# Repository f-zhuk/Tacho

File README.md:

# Tacho
ER11 spindle tachometer with rotating display output

Demonstration video:
https://youtu.be/U8TMPHPOaX0?si=c8lLyx_i4HfSOsvz

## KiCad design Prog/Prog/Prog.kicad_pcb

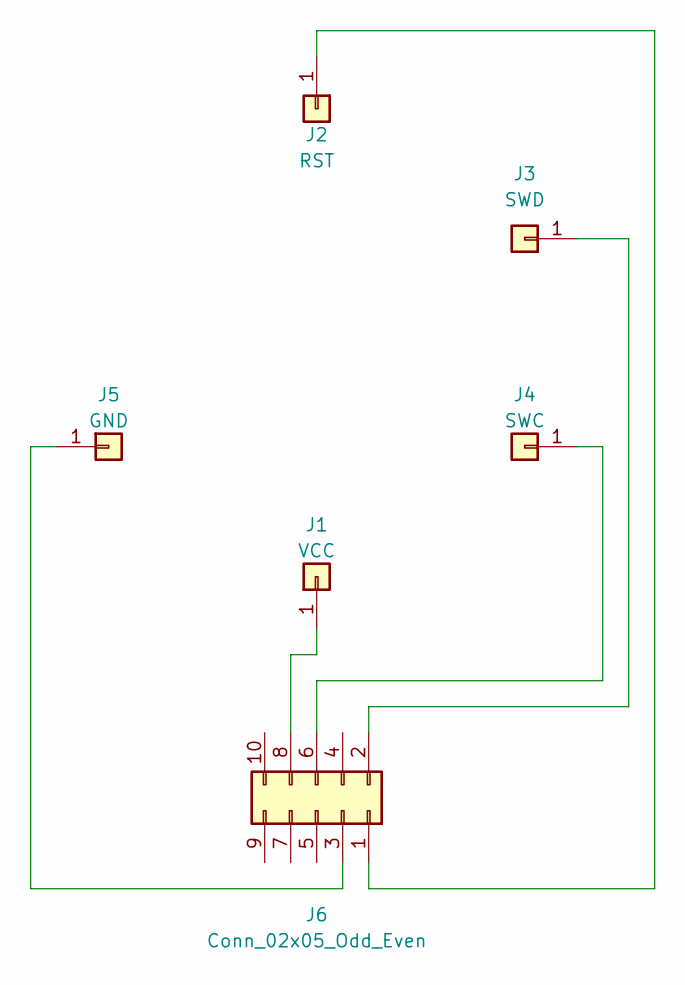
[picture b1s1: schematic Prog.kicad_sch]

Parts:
J1: VCC; PinHeader_1x01_P2.54mm_Vertical
J2: RST; PinHeader_1x01_P2.54mm_Vertical
J3: SWD; PinHeader_1x01_P2.54mm_Vertical
J4: SWC; PinHeader_1x01_P2.54mm_Vertical
J5: GND; PinHeader_1x01_P2.54mm_Vertical
J6: Conn_02x05_Odd_Even; IDC-Header_2x05_P2.54mm_Vertical

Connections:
unnamed: J1.1, J6.8
unnamed: J2.1, J6.1
unnamed: J3.1, J6.2
unnamed: J4.1, J6.6
unnamed: J5.1, J6.3

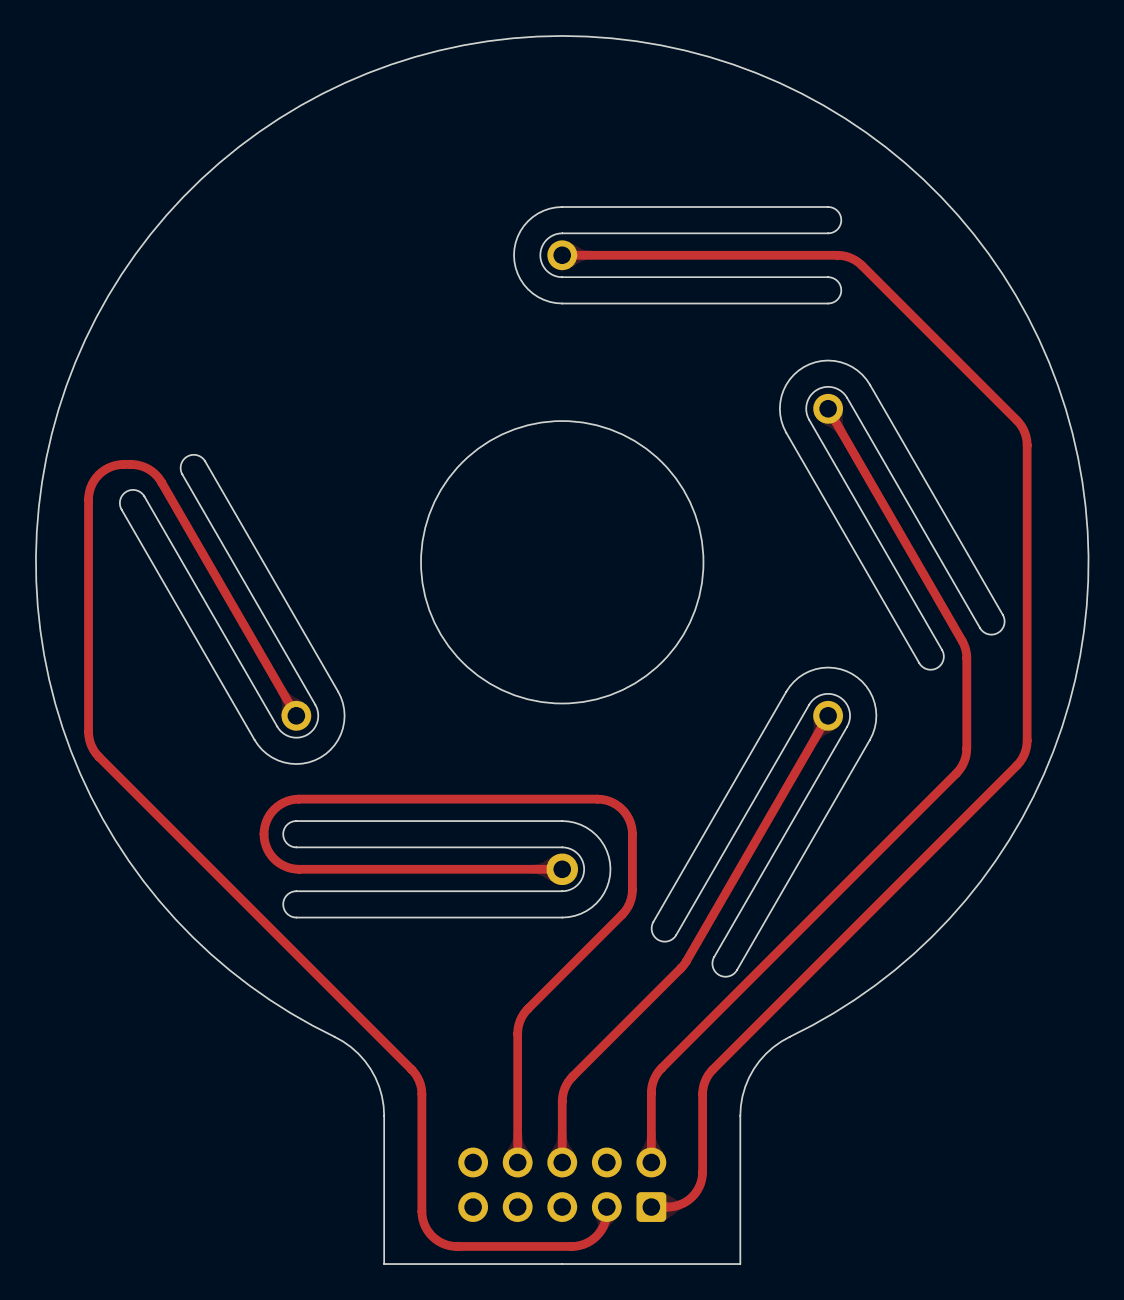
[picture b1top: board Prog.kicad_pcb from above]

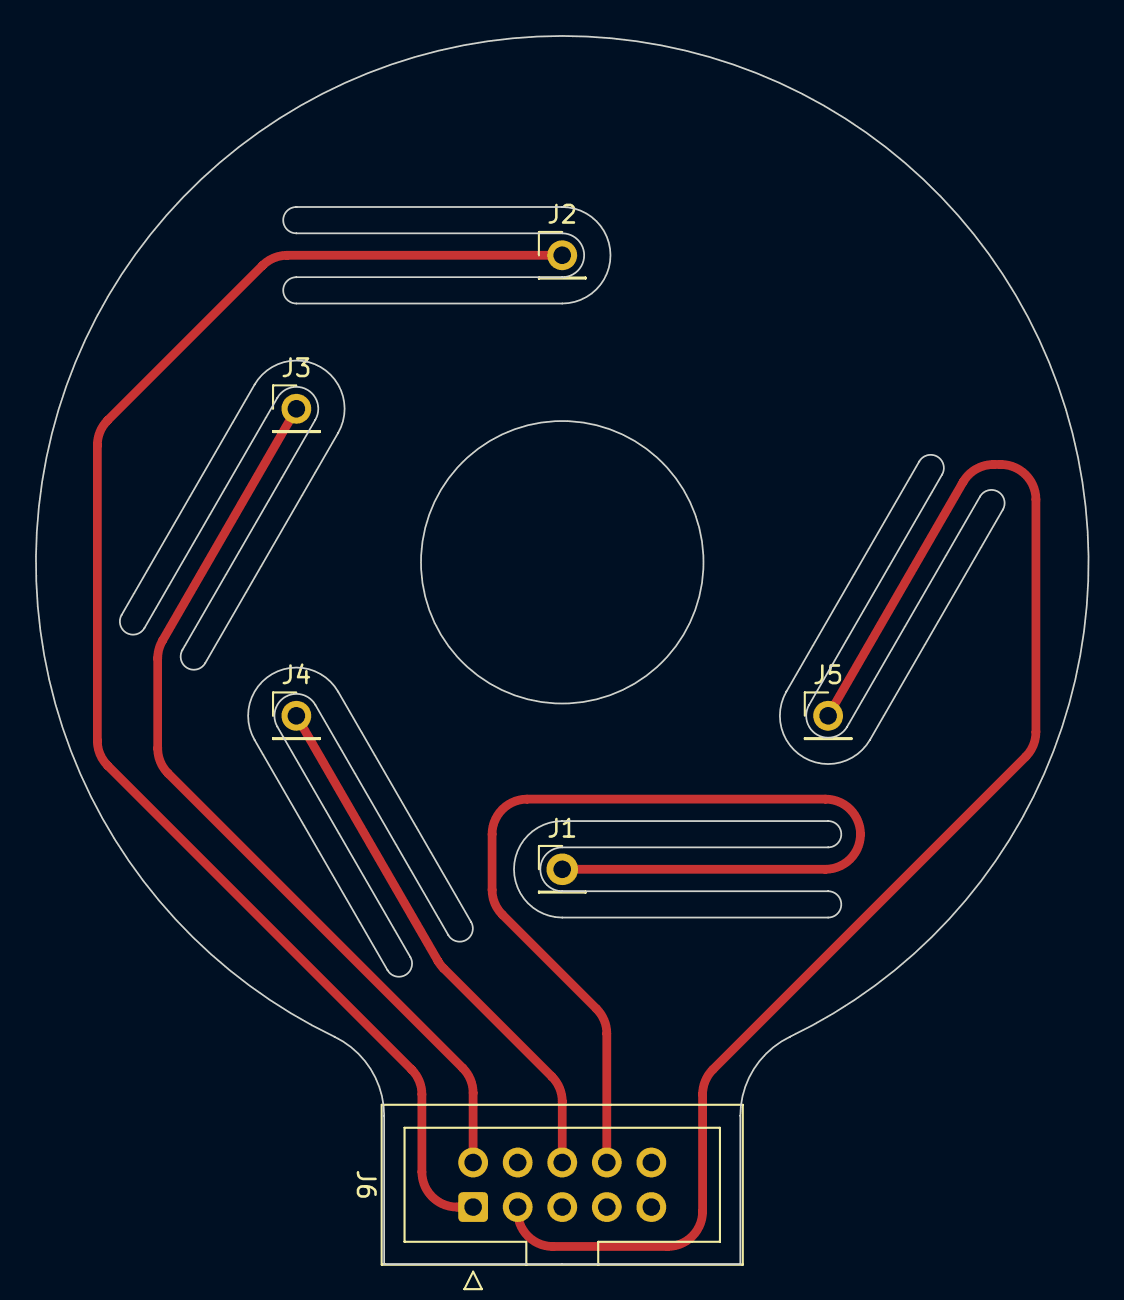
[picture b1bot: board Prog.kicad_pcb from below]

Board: 2 copper layers, 60.0 x 70.0 mm, 6 parts (6 on the bottom side), 5 nets.

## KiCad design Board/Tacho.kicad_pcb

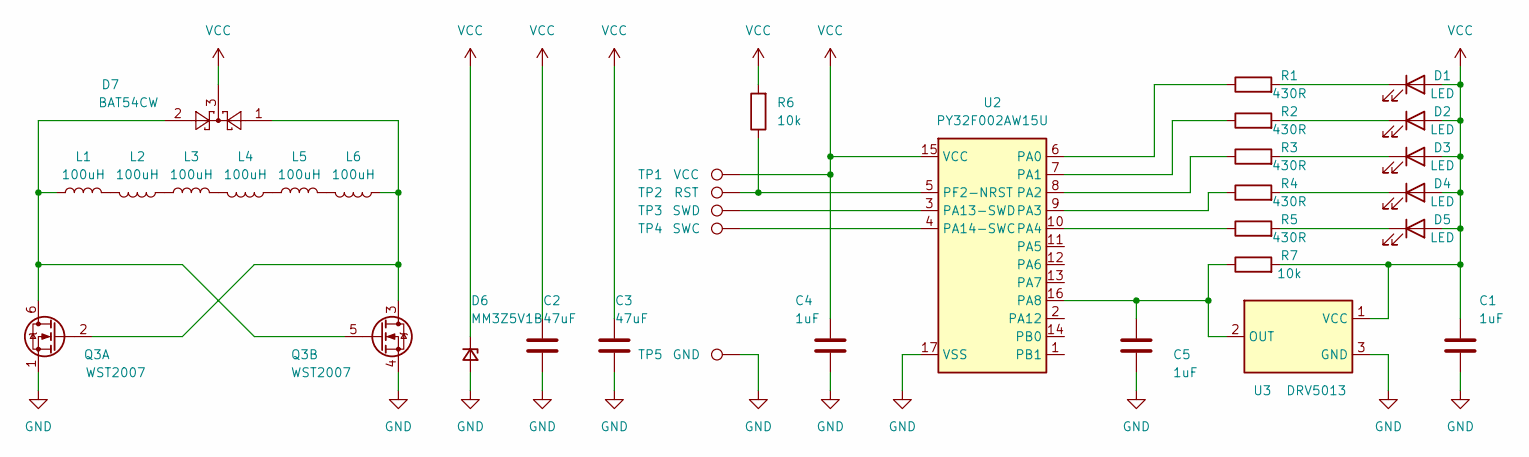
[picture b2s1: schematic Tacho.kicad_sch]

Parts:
C1, C4, C5: 1uF; C_0402_1005Metric_Pad0.74x0.62mm_HandSolder
C2, C3: 47uF; C_0805_2012Metric_Pad1.18x1.45mm_HandSolder
D1, D2, D3, D4, D5: LED; LED_0402_1005Metric
D6: MM3Z5V1B; D_SOD-323
D7: BAT54CW; SOT-323_SC-70
L1, L2, L3, L4, L5, L6: 100uH; L_SHOUHAN _CY43-100UH
Q3: WST2007; SOT-363_SC-70-6
R1, R2, R3, R4, R5: 430R; R_0402_1005Metric
R6, R7: 10k; R_0402_1005Metric
TP1: VCC; TestPoint_Pad_D2.0mm
TP2: RST; TestPoint_Pad_D2.0mm
TP3: SWD; TestPoint_Pad_D2.0mm
TP4: SWC; TestPoint_Pad_D2.0mm
TP5: GND; TestPoint_Pad_D2.0mm
U2: PY32F002AW15U; QFN-16-1EP_3x3mm_P0.5mm_EP1.7x1.7mm
U3: DRV5013; SOT-23

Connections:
GND: C1.2, C2.2, C3.2, C4.2, C5.2, D6.2 (A), Q3.1 (S), Q3.4 (S), TP5.1, U2.17 (VSS), U3.3 (GND)
unnamed: D1.1 (K), R1.2
unnamed: D2.1 (K), R2.2
unnamed: D3.1 (K), R3.2
unnamed: D4.1 (K), R4.2
unnamed: D5.1 (K), R5.2
unnamed: L1.2, L2.2
unnamed: L2.1, L3.1
unnamed: L3.2, L4.2
unnamed: L4.1, L5.1
unnamed: L5.2, L6.2
unnamed: D7.2, L1.1, Q3.5 (G), Q3.6 (D)
unnamed: D7.1, L6.1, Q3.2 (G), Q3.3 (D)
unnamed: R1.1, U2.6 (PA0)
unnamed: R2.1, U2.7 (PA1)
unnamed: R3.1, U2.8 (PA2)
unnamed: R4.1, U2.9 (PA3)
unnamed: R5.1, U2.10 (PA4)
unnamed: C5.1, R7.1, U2.16 (PA8), U3.2 (OUT)
unnamed: TP3.1, U2.3 (PA13-SWD)
unnamed: TP4.1, U2.4 (PA14-SWC)
unnamed: R6.1, TP2.1, U2.5 (PF2-NRST)
VCC: C1.1, C2.1, C3.1, C4.1, D1.2 (A), D2.2 (A), D3.2 (A), D4.2 (A), D5.2 (A), D6.1 (K), D7.3, R6.2, R7.2, TP1.1, U2.15 (VCC), U3.1 (VCC)

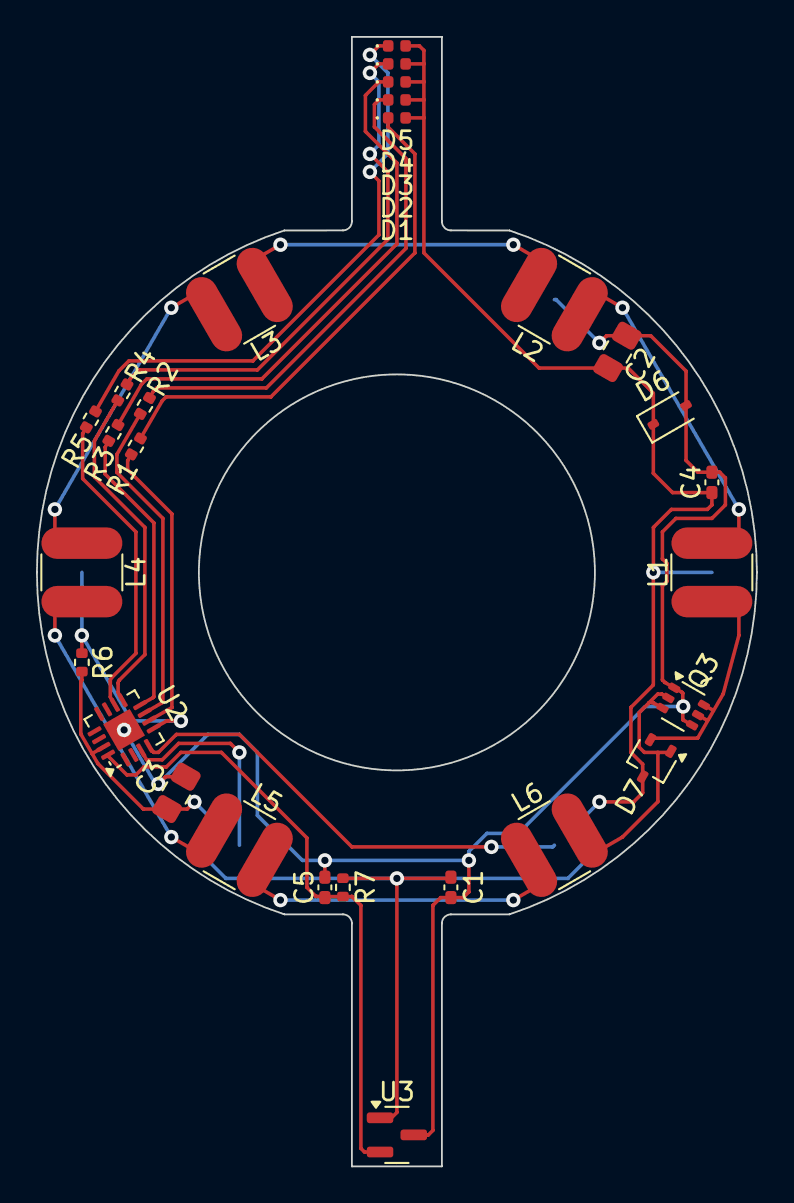
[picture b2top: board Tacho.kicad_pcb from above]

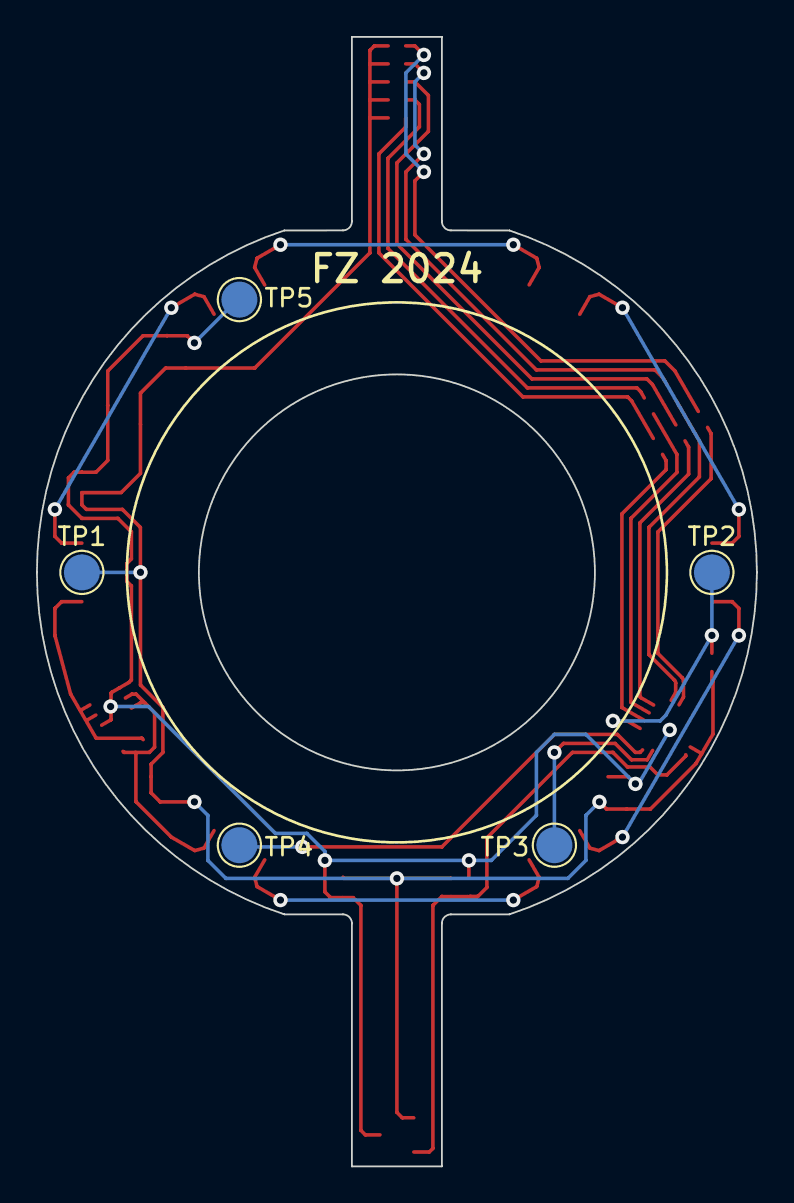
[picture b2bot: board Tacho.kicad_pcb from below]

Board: 2 copper layers, 40.0 x 62.8 mm, 33 parts (5 on the bottom side), 23 nets.

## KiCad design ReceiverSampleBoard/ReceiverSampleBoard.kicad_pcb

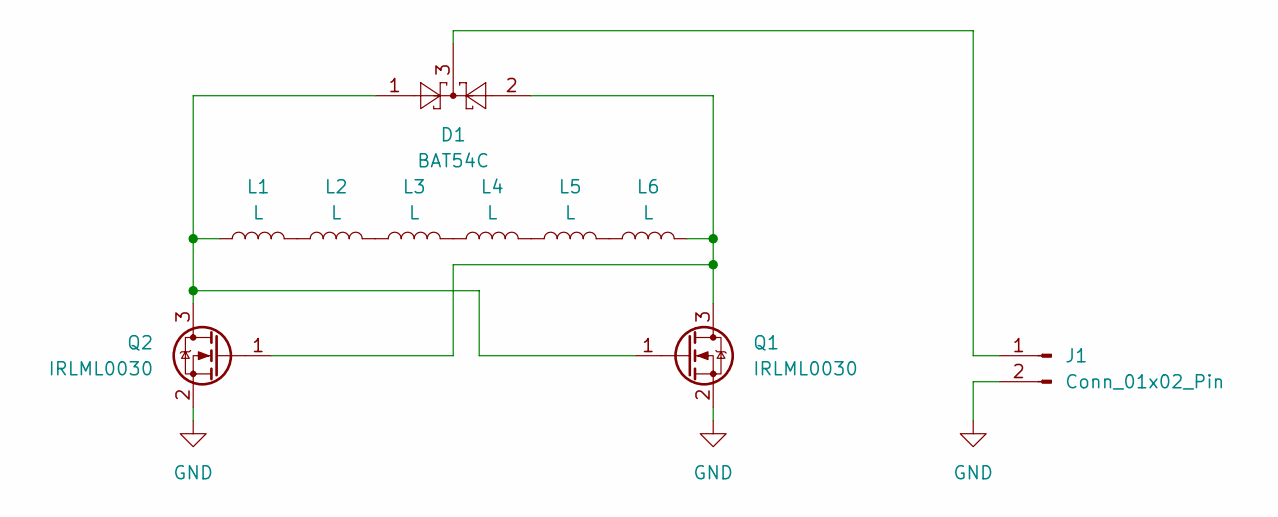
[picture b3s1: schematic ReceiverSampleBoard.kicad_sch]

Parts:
D1: BAT54C; SOT-23
J1: Conn_01x02_Pin; PinHeader_1x02_P2.54mm_Horizontal
L1, L2, L3, L4, L5, L6: L; L_Bourns_SRN8040TA
Q1, Q2: IRLML0030; SOT-23

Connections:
GND: J1.2, Q1.2 (S), Q2.2 (S)
unnamed: D1.3, J1.1
unnamed: L1.2, L2.1
unnamed: L2.2, L3.1
unnamed: L3.2, L4.1
unnamed: L4.2, L5.1
unnamed: L5.2, L6.1
unnamed: D1.2, L6.2, Q1.3 (D), Q2.1 (G)
unnamed: D1.1, L1.1, Q1.1 (G), Q2.3 (D)

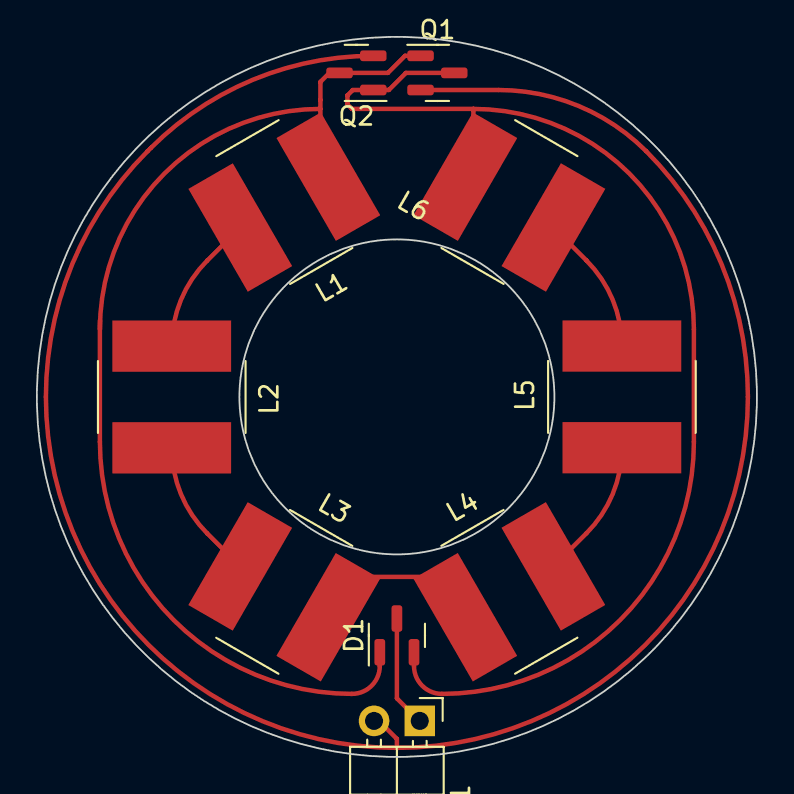
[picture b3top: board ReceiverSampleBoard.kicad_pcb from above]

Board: 2 copper layers, 40.0 x 40.0 mm, 10 parts (0 on the bottom side), 9 nets.

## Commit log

2024-01-22 Initial
2024-01-28 Mechanicals added
2024-02-03 Sample board for measurements in static installation
2024-02-05 Traced Sample board
2024-03-10 Generated Fab files for the test receiver board
2024-03-15 CNC route for copper updated
2024-05-12 Schematic done
2024-05-18 Mechanical updates
2024-05-23 Moved magnets closer to coils, thinned walls
2024-06-10 Updates to pcb
2024-06-30 Layout finished
2024-07-15 Stator mechanics updated
2024-07-20 Stator design update - screws between halves added
2024-07-22 Unsuccessful rotor model, needs to redesign
2024-07-25 Soft part started
2024-07-25 Schematic PDF added for convenience
2024-07-25 Current limit and reset pullup resistors value changed
2024-07-26 Added Programming adapter project
2024-07-27 Moved exports into FAB directory and updated origin
2024-07-27 Adding manufacturing files
2024-07-29 10kHz timer blink at A1
2024-07-29 Same 10kHz but in one-pulse mode
2024-07-30 10kHz toggle at A0 and hall state at A3 (polling)
2024-08-17 NC added for mag retainer and cartridge
2024-08-19 Board updated
2024-08-19 Updated magnet holder parts
2024-08-24 Configuring measure timer
2024-08-25 First text on screen (unfirtynately vertically mirrored)
2024-08-27 GLCD custom font project aded
2024-08-27 RPM Done
2024-08-27 Main functionality finished
2024-08-29 Exported models
2024-08-29 Cover model optimized for SLA created, added
2024-09-08 retainer model for milling designed
2024-09-15 Updated numeric control code for magretainer part
2024-09-21 PDF of prog board exported for toner thermal transfer
